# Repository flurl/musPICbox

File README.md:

# musPICbox

Dies ist das Sourcecode Repository zu meinem Artikel in [Make](https://www.heise.de/make) 3/26, Seite 88.

Außerdem finden Sie hier eine detailiertere Anleitung zum Konfigurieren des µC mit dem MPLAB Code Configurator.

## Konfiguration des PIC mittels MCC

Der MPLAB Code Configurator ermöglicht die grafische Konfiguration diverser Peripherie (Clock, Timer, ADC, PWM etc.) des Microcontrollers per Mausklick. Aus den getroffenen Einstellungen erzeugt der MCC Initialisierungscode, der die Register korrekt setzt und Helferfunktionen bereitstellt.

Die Konfiguration der Pins für die LEDs veranschaulicht diesen Prozess. Nach dem Start des MCC befindet man sich in dessen Hauptfenster, dem `Application Builder`. Hier wird eine grafische Repräsentation der Firmware angezeigt. Der oberste Abschnitt zeigt alle vom User hinzugefügten Komponenten an. Momentan ist das nur die Datei `main.c`. Der mit `System` beschriftete Bereich listet die in Verwendung befindlichen System Treiber. Darunter ist der Device Abschnitt, der Infos über die MCU und ihre Fähigkeiten anzeigt. Die weißen ? auf blauen Hintergrund führen direkt zur Online Dokumentation der jeweiligen Komponenten oder UI-Elemente - sehr praktisch.

Durch einen Klick auf den `Pins` System Treiber öffnet man die `Pin Package View`. Links oben gibt es ein mit "Package" beschriftetes Drop-Down, womit man die Gehäuseform des µC festlegen kann. Wir wählen PDIP20, woraufhin im Arbeitsbereich ein Piktogramm des Chips dargestellt wird. Dem Schaltplan ist zu entnehmen, dass die LEDs mit den GPIOs `RC0`, `RC1` sowie `RC2` verbunden werden. Um dies dem MCC mitzuteilen, klicken wir nacheinander auf die entsprechenden Pins des Symbolbildes, woraufhin ein Pop-Up erscheint, mit dem wir den Pins die Funktion "GPIO | GPIO | Output" zuweisen. Daraufhin wird für jeden Pin im rechten Fenster eine Zeile zur weiteren Konfiguration hinzugefügt. In der Spalte `Custom Name` kann man einen Alias für den jeweiligen IO-Port hinterlegen, den man im Quellcode verwenden kann. Ich habe ihnen dem Schaltplan entsprechend die Namen "LED_RED", "LED_BLUE" und "LED_GREEN" zugewiesen . Außerdem ist bei allen drei LED Pins die Option `Start High` zu aktivieren. Die sorgt dafür, dass die Pins beim Booten bereits auf High gesetzt werden, was, da die LEDs "active-low" verdrahtet sind, den Effekt hat, dass keine der LEDs leuchtet.

Danach wählt man am linken Rand des MCC den Tab `Project Resource` und klickt auf den blauen Button `Generate` im linken oberen Eck. Im `Output` Fenster sieht man, welche Aktionen der MCC sodann ausführt. So erstellt er diverse Dateien im Unterverzeichnis `mmcc_generated_files/system`. In eben jenem Verzeichnis findet sich nun auch eine Datei `pins.h`. Deren Inhalt illustriert, welche Arbeit der MCC für einen übernimmt. Vor allem erstellt der MCC eine Menge Präprozessordirektiven, die uns das lästige direkte hantieren mit den Registern des Prozessors ersparen und den Umgang mit der Peripherie wesentlich vereinfachen.

Die Zeile

```C
#define LED_RED_SetHigh() do { LATCbits.LATC0 = 1; } while(0)
```

ermöglicht es beispielsweise, den Pin, an dem die rote LED hängt (hier kommen die `Custom Names` ins Spiel), durch ein simples `LED_RED_SetHigh()` im C-Code auf High zu setzen. Das Macro `LED_RED_SetHigh()` wird dabei durch den etwas seltsam anmutenden `do ... while(0)` Block ersetzt. Dieser setzt des Bit 0 im `LATC` Register auf 1 und damit den Pin auf High. Die Konstruktion mit der do-while-Schleife hat syntaktische Gründe.

Der MCC ist auch die passende Anlaufstelle um die Frequenz, mit der µC läuft einzustellen. Die Frequenzen, die wir für die Erzeugung der Töne benötigen, liegen im niedrigen kHz Bereich. Es ergibt daher wenig sinn, den PIC mit vollem Speed laufen zu lassen. Je langsamnr, desto niedriger der Stromverbrauch. Ein Klick auf das `Clock Control` Modul ermöglicht es, den Takt mit dem Dropdown `HF Internal Clock` auf 1MHz zu setzen.

Um die weiteren GPIOs zu konfigurieren gehen wir nach dem selben Muster vor. Dem Schaltplan nach wird der Taster mit dem Pin `RA2` verbunden. Also klicken wir im `Pin Package View` des MCC auf das Symbol des entsprechenden Pins und weisen ihm die Funktion "GPIO | Input" zu. Als `Custom Name` verwende ich "PIN_BTN". Außerdem setze ich das Häckchen bei `Weak Pullup`, womit der interen Pullup Widerstand aktiviert wird.

Damit ist der "einfache" Part der Konfiguration erledigt. Nun gilt es noch zwei Probleme zu lösen. Das erste ist, dass, um eine wirklich (pseudo)-zufällige Wiedergabe zu ermöglichen, wir noch einen Seed für den Zufallsgenerator benötigen. Dafür machen wir uns einen floatenden analogen Eingang zu nutze. Floatend bedeutet, dass er nicht weiter verdrahtet und somit nur einem Zufallsrauschen ausgesetzt ist. Dafür müssen wir zuerst ins `Application Builder` Fenster zurück und mittels des Knopfes `⊕Add Component` den Add Component Dialog aufrufen. Am besten filtert man in diesem die Liste der verfügbaren Komponenten, indem man ins Suchfeld den Begriff "ADC" eingibt. In den Suchergebnissen klickt man schließlich in der Zeile des ADC Moduls ganz rechts auf das ⊕ Symbol, woraufhin sich der Dialog schließt und im `Application Builder` View das neu hinzugefügte Modul unter Main angezeigt wird. Mit dem blauen Zahnradsymbol in der rosanen Komponentenbox gelangt man zur Konfiguation des ADC. Wir belassen alles auf den Standardwerten, aber ein Blick auf die angebotenen Möglichkeiten lohnt sich allemal.

Im `Pins`-Reiter sieht man auch, dass der Pin `RA0` automatisch dem ADC Modul zugewiesen wurde.

Was jetzt noch fehlt sind die zwei Pins, die das PWM Signal ausgeben sollen. Dazu sind zwei weitere Komponenten notwendig, die man wieder im `Application Builder` mittels `⊕Add Component` hinzufügen kann. Das erste ist das "CCP1" (Capture/Compare/PWM) Modul, das zweite heißt "CLC1" (Configurable Logic Cell). Nach beiden sucht man im Add Component Dialog und inkludiert sie ins Projekt mit ⊕.

Das blaue Zahnradsymbol beim "CCP1" Modul öffnet dessen Konfigurationsoptionen am rechten Rand. Den `CCP Mode` setzen wir auf PWM, was neue Optionen zum Vorschein bringt. Wählen wir nun im `TMR Dependency Selector` "TMR2" aus, wird der Timer2 als Abhängigkeit zu den Projektresourcen hinzugefügt (Reiter am linken Rand des MCC). Da die PWM und Timer Konfiguration dynamisch während des Programmablaufs geändert wird, können wir die restlichen Einstellungen auf dem Standard belassen.

Fehlt noch das CLC1 Modul. Wie bereits erwähnt, ermöglicht dieses, diverse Input Signale mit Logikblöcken zu verbinden und daraus ein Ausgangsignal zu generieren - ganz unabhängig vom Programmcode. Ein Klick auf die Komponente im `Application Builder` öffnet wiederum die Einstellungen des Moduls. Im `Logic Cell Mode bits` Dropdown bietet sich die "4-input-AND" Schaltung an. Sobald man sie ausgewählt hat, updated sich der Schaltplan im unteren Fenster und zeigt den Aufbau der Logikschaltung. Die mag auf den ersten Blick etwas ehrfurchtgebietend wirken, ist aber gar nicht kompliziert, wenn man sich in kleinen Schritten herantastet.

Unser Ziel ist es, das PWM Signal zu invertieren. Also ist es nur logisch, dass das PWM Signal als Input herhalten muss. Dafür reicht es, im ersten Dropdown den Ouptut des "CCP1" Moduls auszuwählen. Die erste Stufe der Schaltung besteht aus vier vierfach ODER Verknüpfungen, die zweite aus einer vierfach UND Verknüpfung und die dritte aus einem Buffer. Wenn man nun das Eingangssignal mit allen vier ODER Verknüpfungen verbindet, in dem man auf das strichlierte Quadrat auf der Eingangsseite der ODER Symbole klickt, bis sie mit dem Eingangssignal durch eine durchgehende Linie verbunden sind, wird das Signal direkt an alle vier Eingänge des AND Logikblocks angelegt. Das heißt, spuckt das "CCP1" eine 1 aus, liegt auch am Ausgang des ANDs eine 1 an. Diese wird nun noch durch den Buffer geschickt - der nichts anderes macht, als das Eingangssignal an seinen Ausgang durchzureichen - und wir erhalten am Ausgang der Logikzelle eine Kopie des Eingangssignals. Ziel fast erreicht; durch einen Klick auf das strichlierte Quadrat am Ausgang des Buffers fügen wir noch ein NOT-Gate hinzu, welches das Ausgangsignal des Buffers invertiert. Und somit ist nun das Ausgangssignal des "CLC1" Moduls stets invertiert zum PWM Signal.

Als letzten Schritt müssen noch die Ausgänge der Module den entsprechenden Pins zugewiesen werden. Also zurück zur `Pin Package View`. Der Buzzer ist laut Schaltplan mit den Pins `RC3` und `RC4` verbunden. Deshalb weisen wir einem von ihnen "CCP1 | CCP1OUT | output" zu, und dem anderen "CLC1 | CLC1 | output". Welcher welche Rolle übernimmt ist egal, da sie immer gegengleich betrieben werden.

Somit ist das Setup im MCC abgeschlossen und mit der `Generate`-Schaltfläche lassen wir die notwendigen Dateien vom MCC erzeugen.

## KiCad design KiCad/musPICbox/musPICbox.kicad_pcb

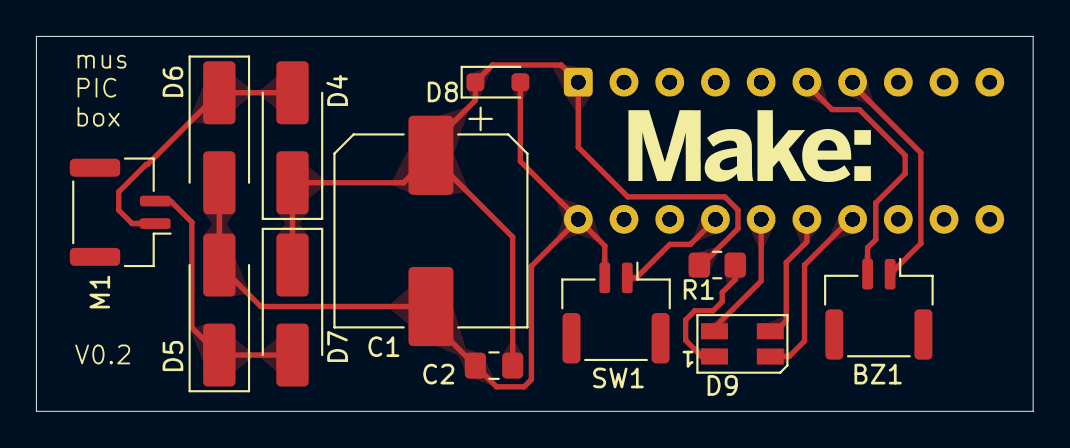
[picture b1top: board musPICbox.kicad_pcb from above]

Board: 2 copper layers, 55.4 x 20.8 mm, 13 parts (1 on the bottom side), 11 nets.

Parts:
BZ1: Buzzer; JST_GH_BM02B-GHS-TBT_1x02-1MP_P1.25mm_Vertical
C1: 1000µ; CP_Elec_10x10.5
C2: 0.1µ; C_0805_2012Metric_Pad1.18x1.45mm_HandSolder
D4, D5, D6, D7: D_Schottky; D_SMA_Handsoldering
D8: D_Zener 5.1V; D_SOD-323_HandSoldering
D9: LED_ARGB; LED_RGB_Wuerth-PLCC4_3.2x2.8mm_150141M173100
M1: Motor_DC; JST_GH_BM02B-GHS-TBT_1x02-1MP_P1.25mm_Vertical
R1: 470; R_0805_2012Metric_Pad1.20x1.40mm_HandSolder
SW1: SW_Push; JST_GH_BM02B-GHS-TBT_1x02-1MP_P1.25mm_Vertical
U1: PIC16F18346-P; DIP-20_W7.62mm

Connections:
GND: C1.2, C2.2, D4.2 (A), D5.2 (A), D8.2 (A), SW1.2, U1.20 (VSS)
unnamed: BZ1.1 (+), U1.7 (RC3)
unnamed: BZ1.2 (-), U1.6 (RC4)
unnamed: D4.1 (K), D6.2 (A), M1.1 (+)
unnamed: D5.1 (K), D7.2 (A), M1.2 (-)
unnamed: C1.1, C2.1, D6.1 (K), D7.1 (K), D8.1 (K), R1.2, U1.1 (VDD)
unnamed: D9.1 (A), R1.1
unnamed: D9.4 (BK), U1.15 (RC1)
unnamed: D9.3 (GK), U1.14 (RC2)
unnamed: D9.2 (RK), U1.16 (RC0)
unnamed: SW1.1, U1.17 (RA2)

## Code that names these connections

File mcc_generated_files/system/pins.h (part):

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// get/set IO_RA2 aliases
#define PIN_BTN_TRIS                 TRISAbits.TRISA2
#define PIN_BTN_LAT                  LATAbits.LATA2
#define PIN_BTN_PORT                 PORTAbits.RA2
#define PIN_BTN_WPU                  WPUAbits.WPUA2
#define PIN_BTN_OD                   ODCONAbits.ODCA2
#define PIN_BTN_ANS                  ANSELAbits.ANSA2
#define PIN_BTN_SetHigh()            do { LATAbits.LATA2 = 1; } while(0)
#define PIN_BTN_SetLow()             do { LATAbits.LATA2 = 0; } while(0)
#define PIN_BTN_Toggle()             do { LATAbits.LATA2 = ~LATAbits.LATA2; } while(0)
#define PIN_BTN_GetValue()           PORTAbits.RA2
#define PIN_BTN_SetDigitalInput()    do { TRISAbits.TRISA2 = 1; } while(0)
#define PIN_BTN_SetDigitalOutput()   do { TRISAbits.TRISA2 = 0; } while(0)
#define PIN_BTN_SetPullup()          do { WPUAbits.WPUA2 = 1; } while(0)
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// get/set IO_RC0 aliases
#define LED_BLUE_TRIS                 TRISCbits.TRISC0
#define LED_BLUE_LAT                  LATCbits.LATC0
#define LED_BLUE_PORT                 PORTCbits.RC0
#define LED_BLUE_WPU                  WPUCbits.WPUC0
#define LED_BLUE_OD                   ODCONCbits.ODCC0
#define LED_BLUE_ANS                  ANSELCbits.ANSC0
#define LED_BLUE_SetHigh()            do { LATCbits.LATC0 = 1; } while(0)
#define LED_BLUE_SetLow()             do { LATCbits.LATC0 = 0; } while(0)
#define LED_BLUE_Toggle()             do { LATCbits.LATC0 = ~LATCbits.LATC0; } while(0)
#define LED_BLUE_GetValue()           PORTCbits.RC0
#define LED_BLUE_SetDigitalInput()    do { TRISCbits.TRISC0 = 1; } while(0)
#define LED_BLUE_SetDigitalOutput()   do { TRISCbits.TRISC0 = 0; } while(0)
#define LED_BLUE_SetPullup()          do { WPUCbits.WPUC0 = 1; } while(0)
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// get/set IO_RC1 aliases
#define LED_GREEN_TRIS                 TRISCbits.TRISC1
#define LED_GREEN_LAT                  LATCbits.LATC1
#define LED_GREEN_PORT                 PORTCbits.RC1
#define LED_GREEN_WPU                  WPUCbits.WPUC1
#define LED_GREEN_OD                   ODCONCbits.ODCC1
#define LED_GREEN_ANS                  ANSELCbits.ANSC1
#define LED_GREEN_SetHigh()            do { LATCbits.LATC1 = 1; } while(0)
#define LED_GREEN_SetLow()             do { LATCbits.LATC1 = 0; } while(0)
#define LED_GREEN_Toggle()             do { LATCbits.LATC1 = ~LATCbits.LATC1; } while(0)
#define LED_GREEN_GetValue()           PORTCbits.RC1
#define LED_GREEN_SetDigitalInput()    do { TRISCbits.TRISC1 = 1; } while(0)
#define LED_GREEN_SetDigitalOutput()   do { TRISCbits.TRISC1 = 0; } while(0)
#define LED_GREEN_SetPullup()          do { WPUCbits.WPUC1 = 1; } while(0)
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// get/set IO_RC2 aliases
#define LED_RED_TRIS                 TRISCbits.TRISC2
#define LED_RED_LAT                  LATCbits.LATC2
#define LED_RED_PORT                 PORTCbits.RC2
#define LED_RED_WPU                  WPUCbits.WPUC2
#define LED_RED_OD                   ODCONCbits.ODCC2
#define LED_RED_ANS                  ANSELCbits.ANSC2
#define LED_RED_SetHigh()            do { LATCbits.LATC2 = 1; } while(0)
#define LED_RED_SetLow()             do { LATCbits.LATC2 = 0; } while(0)
#define LED_RED_Toggle()             do { LATCbits.LATC2 = ~LATCbits.LATC2; } while(0)
#define LED_RED_GetValue()           PORTCbits.RC2
#define LED_RED_SetDigitalInput()    do { TRISCbits.TRISC2 = 1; } while(0)
#define LED_RED_SetDigitalOutput()   do { TRISCbits.TRISC2 = 0; } while(0)
#define LED_RED_SetPullup()          do { WPUCbits.WPUC2 = 1; } while(0)
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// get/set IO_RC3 aliases
#define IO_RC3_TRIS                 TRISCbits.TRISC3
#define IO_RC3_LAT                  LATCbits.LATC3
#define IO_RC3_PORT                 PORTCbits.RC3
#define IO_RC3_WPU                  WPUCbits.WPUC3
#define IO_RC3_OD                   ODCONCbits.ODCC3
#define IO_RC3_ANS                  ANSELCbits.ANSC3
#define IO_RC3_SetHigh()            do { LATCbits.LATC3 = 1; } while(0)
#define IO_RC3_SetLow()             do { LATCbits.LATC3 = 0; } while(0)
#define IO_RC3_Toggle()             do { LATCbits.LATC3 = ~LATCbits.LATC3; } while(0)
#define IO_RC3_GetValue()           PORTCbits.RC3
#define IO_RC3_SetDigitalInput()    do { TRISCbits.TRISC3 = 1; } while(0)
#define IO_RC3_SetDigitalOutput()   do { TRISCbits.TRISC3 = 0; } while(0)
#define IO_RC3_SetPullup()          do { WPUCbits.WPUC3 = 1; } while(0)
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// get/set IO_RC4 aliases
#define IO_RC4_TRIS                 TRISCbits.TRISC4
#define IO_RC4_LAT                  LATCbits.LATC4
#define IO_RC4_PORT                 PORTCbits.RC4
#define IO_RC4_WPU                  WPUCbits.WPUC4
#define IO_RC4_OD                   ODCONCbits.ODCC4
#define IO_RC4_ANS                  ANSELCbits.ANSC4
#define IO_RC4_SetHigh()            do { LATCbits.LATC4 = 1; } while(0)
#define IO_RC4_SetLow()             do { LATCbits.LATC4 = 0; } while(0)
#define IO_RC4_Toggle()             do { LATCbits.LATC4 = ~LATCbits.LATC4; } while(0)
#define IO_RC4_GetValue()           PORTCbits.RC4
#define IO_RC4_SetDigitalInput()    do { TRISCbits.TRISC4 = 1; } while(0)
#define IO_RC4_SetDigitalOutput()   do { TRISCbits.TRISC4 = 0; } while(0)
#define IO_RC4_SetPullup()          do { WPUCbits.WPUC4 = 1; } while(0)
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
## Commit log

2026-04-27 Add KiCad files
2026-04-27 Add BOM file
2026-05-19 Add README.md
    Added detailed instructions for configuring the PIC microcontroller using the MPLAB Code Configurator, including steps for setting up GPIOs, ADC, PWM, and logic cells.
2026-05-19 Add images

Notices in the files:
mcc_generated_files/system/pins.h:
© [2026] Microchip Technology Inc. and its subsidiaries.
